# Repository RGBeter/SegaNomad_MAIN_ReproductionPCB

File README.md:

# Sega Nomad MAIN Reproduction PCB
Reproduction of the Sega Nomad's main board, created from scans provided by Villahed94, Sega's documentation, and community knowledge of the FC1004 style Genesis.
Additional features include TMSS bypass jumpers, SMS support and 32X support.

# Build Notes
These PCBs are tested to work with with a stock VENUS SUB pcb, building these requires skills in microsoldering, QFP soldering, hot air rework, and Mega Drive troubleshooting.
It is highly recomendded you start with a set of known working parts from a donor MegaDrive. VA1, VA1.8 and VA3 Model 2 Sega Genesis/MegaDrive can provide all of the necessary custom chips needed for this build.
Support is not officially provided by neither RGBeter nor Villahed94 with building or debugging these PCBs.

# Production Notes
While Sega utlized a 2 layer PCB for the Nomad, it is best to order these as a 4 layer PCB in order to improve noise across the board
If you wish NOT to include the SRES bypass, add the following bodge wires in order to connect the original 315-5684 based SRES circuit.

# BOM
Most of, if not all parts can be directly transplanted from a donor Nomad Main board, however, some alterations have been made, and they are as follows:

R5 + R6, FM DAC limiting resistors best changed to 0 ohms when modding audio

All large MLCC capacitors can have their value increased to 10uF to improve noise

|Component|Value|Note|
|:--------|:----|:---|
|IC1|PLCC 68000|CPU|
|IC2|68K RAM|WORK RAM|
|IC3|FC1004/FF1004|MAIN ASIC|
|IC4|VIDEO RAM|VRAM|
|IC5|QFP Z80|Z80 CPU|
|IC6|Z80 RAM|ZRAM|
|IC7|LM809|SRES BYPASS ONLY|
|C1|10uF|1206 X7R|
|C2|10uF|1206 X7R|
|C3|10uF|1206 X7R|
|C4|47pF|0603 C0G 315-5708 ONLY|
|C5|100pF|0603 C0G|
|C6|100pF|0603 C0G|
|C7|22pF|0603 C0G|
|C8|1000pF|0603 C0G|
|C9|N/A|DOES NOT EXIST|
|C10|100pF|0603 C0G|
|C11|100pF|0603 C0G|
|C12|33pF|0603 C0G|
|C13|N/A|DOES NOT EXIST|
|C14|10uF|1206 X7R|
|C15|10uF|1206 X7R|
|C16|10uF|1206 X7R|
|C17|10uF|1206 X7R|
|C18|20pF|0603 C0G|
|C19|47pF|0603 C0G|
|C20|10uF|1206 X7R|
|C21|33pF|0603 C0G DO NOT POPULATE|
|C22|100pF|0603 C0G|
|C23|33pF|0603 C0G|
|C24|100pF|0603 C0G|
|C25|0.1uF|0603 X7R|
|C26|0.1uF|0603 X7R|
|C27|0.1uF|0603 X7R|
|C28|N/A|DO NOT POPULATE|
|C29|100pF|0603 C0G|
|C30|0.1uF|0603 X7R|
|C31|0.047uF|0603 X7R|
|C32|N/A|DO NOT POPULATE|
|C33|N/A|DOES NOT EXIST|
|C30|1uF|0603 X7R SRES BYPASSS ONLY|
|CE1|47uF 6v|SMD ELEC, CAN REPLACE WITH TANTALUM|
|CE2|47uF 6v|SMD ELEC, CAN REPLACE WITH TANTALUM|
|CE3|100uF 6v|SMD ELEC, CAN REPLACE WITH TANTALUM|
|CE4|47uF 6v|SMD ELEC, CAN REPLACE WITH TANTALUM|
|D1|SOD-923 DIODE|SRES BYPASS ONLY|
|OSC1|MCLK OSCILATOR, SQUARE PACKAGE|CHECK REGION|
|R1|150R|0603|
|R2|220R|0603|
|R3|2.2K|0603|
|R4|220R|0603|
|R5|0R|0603 DAC LIMITING RESISTOR|
|R6|0R|0603 DAC LIMITING RESISTOR|
|R7|2.2K|0603|
|R8|4.7K|0603|
|R9|100R|0603|
|R10|100R|0603|
|R11|2.2K|0603|
|R12|2.2K|0603|
|R13|5.6K|0603|
|R14|5.6K|0603|
|R15|5.6K|0603|
|R16|4.7K|0603|
|R17|4.7K|0603|
|R18|4.7K|0603|
|R19|1.2K|0603|
|R20|1.2K|0603|
|R21|1.2K|0603|
|R22|4.7K|0603|
|R23|1.0K|0603|
|R24|330R|0603|
|R25|330R|0603|
|R26|2.2K|0603|
|R27|100K|0603|
|RA1|4.7K|5X1206 BANK|
|RB1|2.2K|4X0603 BANK|
|RB2|100R|4X0603 BANK|
|RB3|100R|4X0603 BANK|
|RB4|100R|4X0603 BANK|
|RB5|100R|4X0603 BANK|
|RB6|100R|4X0603 BANK|

# Special Thanks
Oleg Endo: Found missing C31 and documented its value, provided EMI filter part numbers

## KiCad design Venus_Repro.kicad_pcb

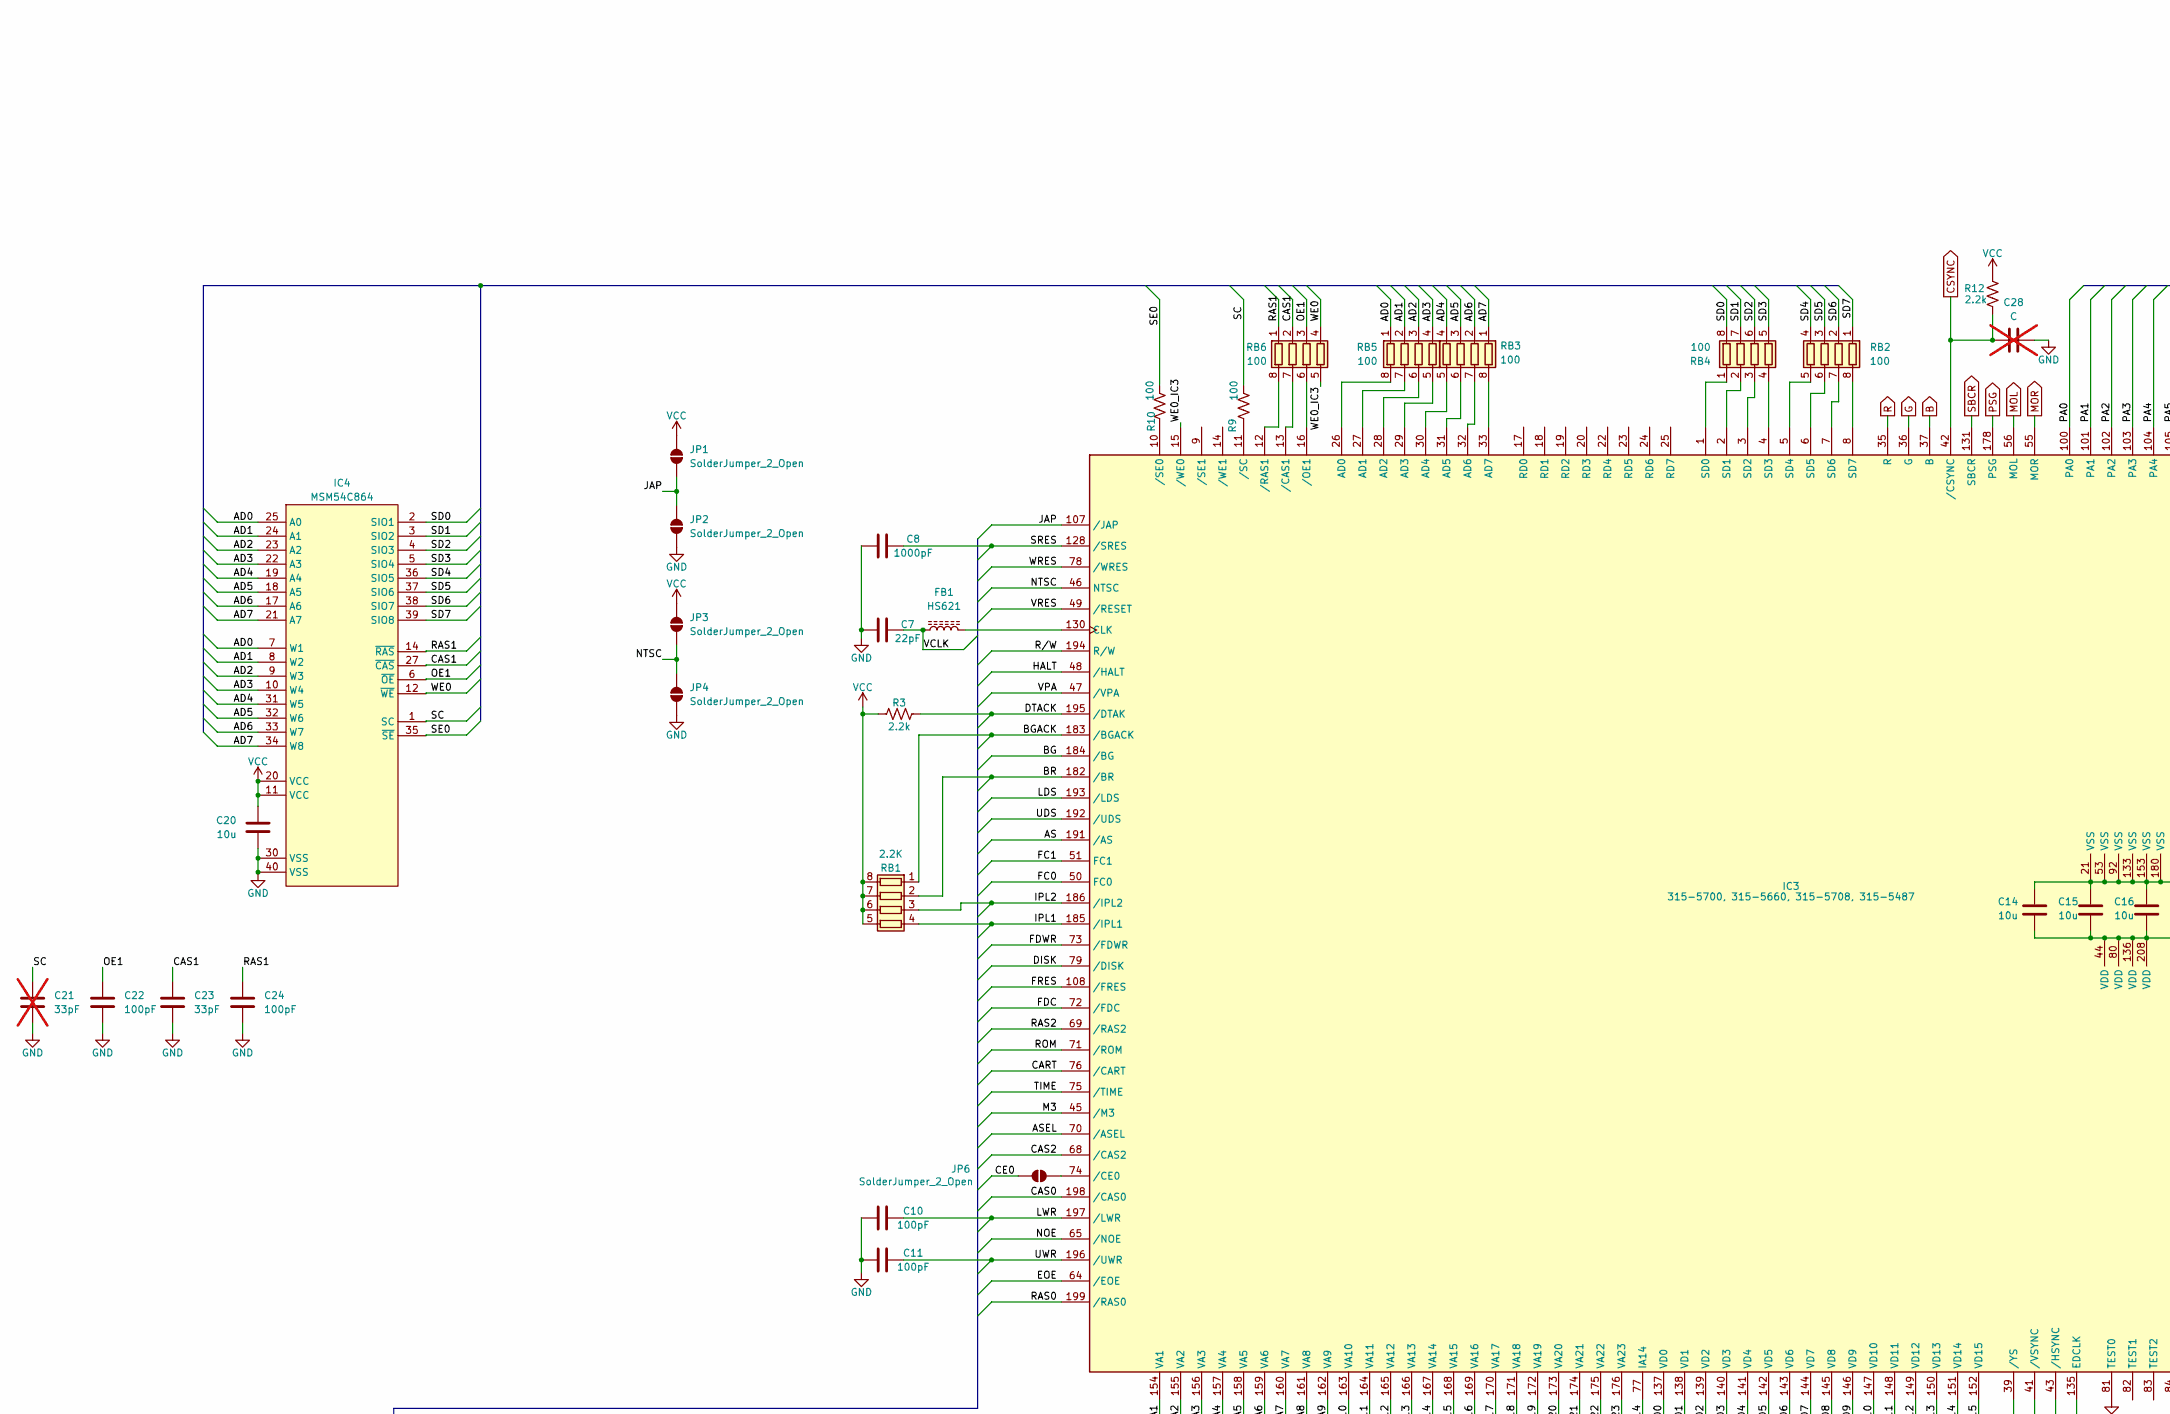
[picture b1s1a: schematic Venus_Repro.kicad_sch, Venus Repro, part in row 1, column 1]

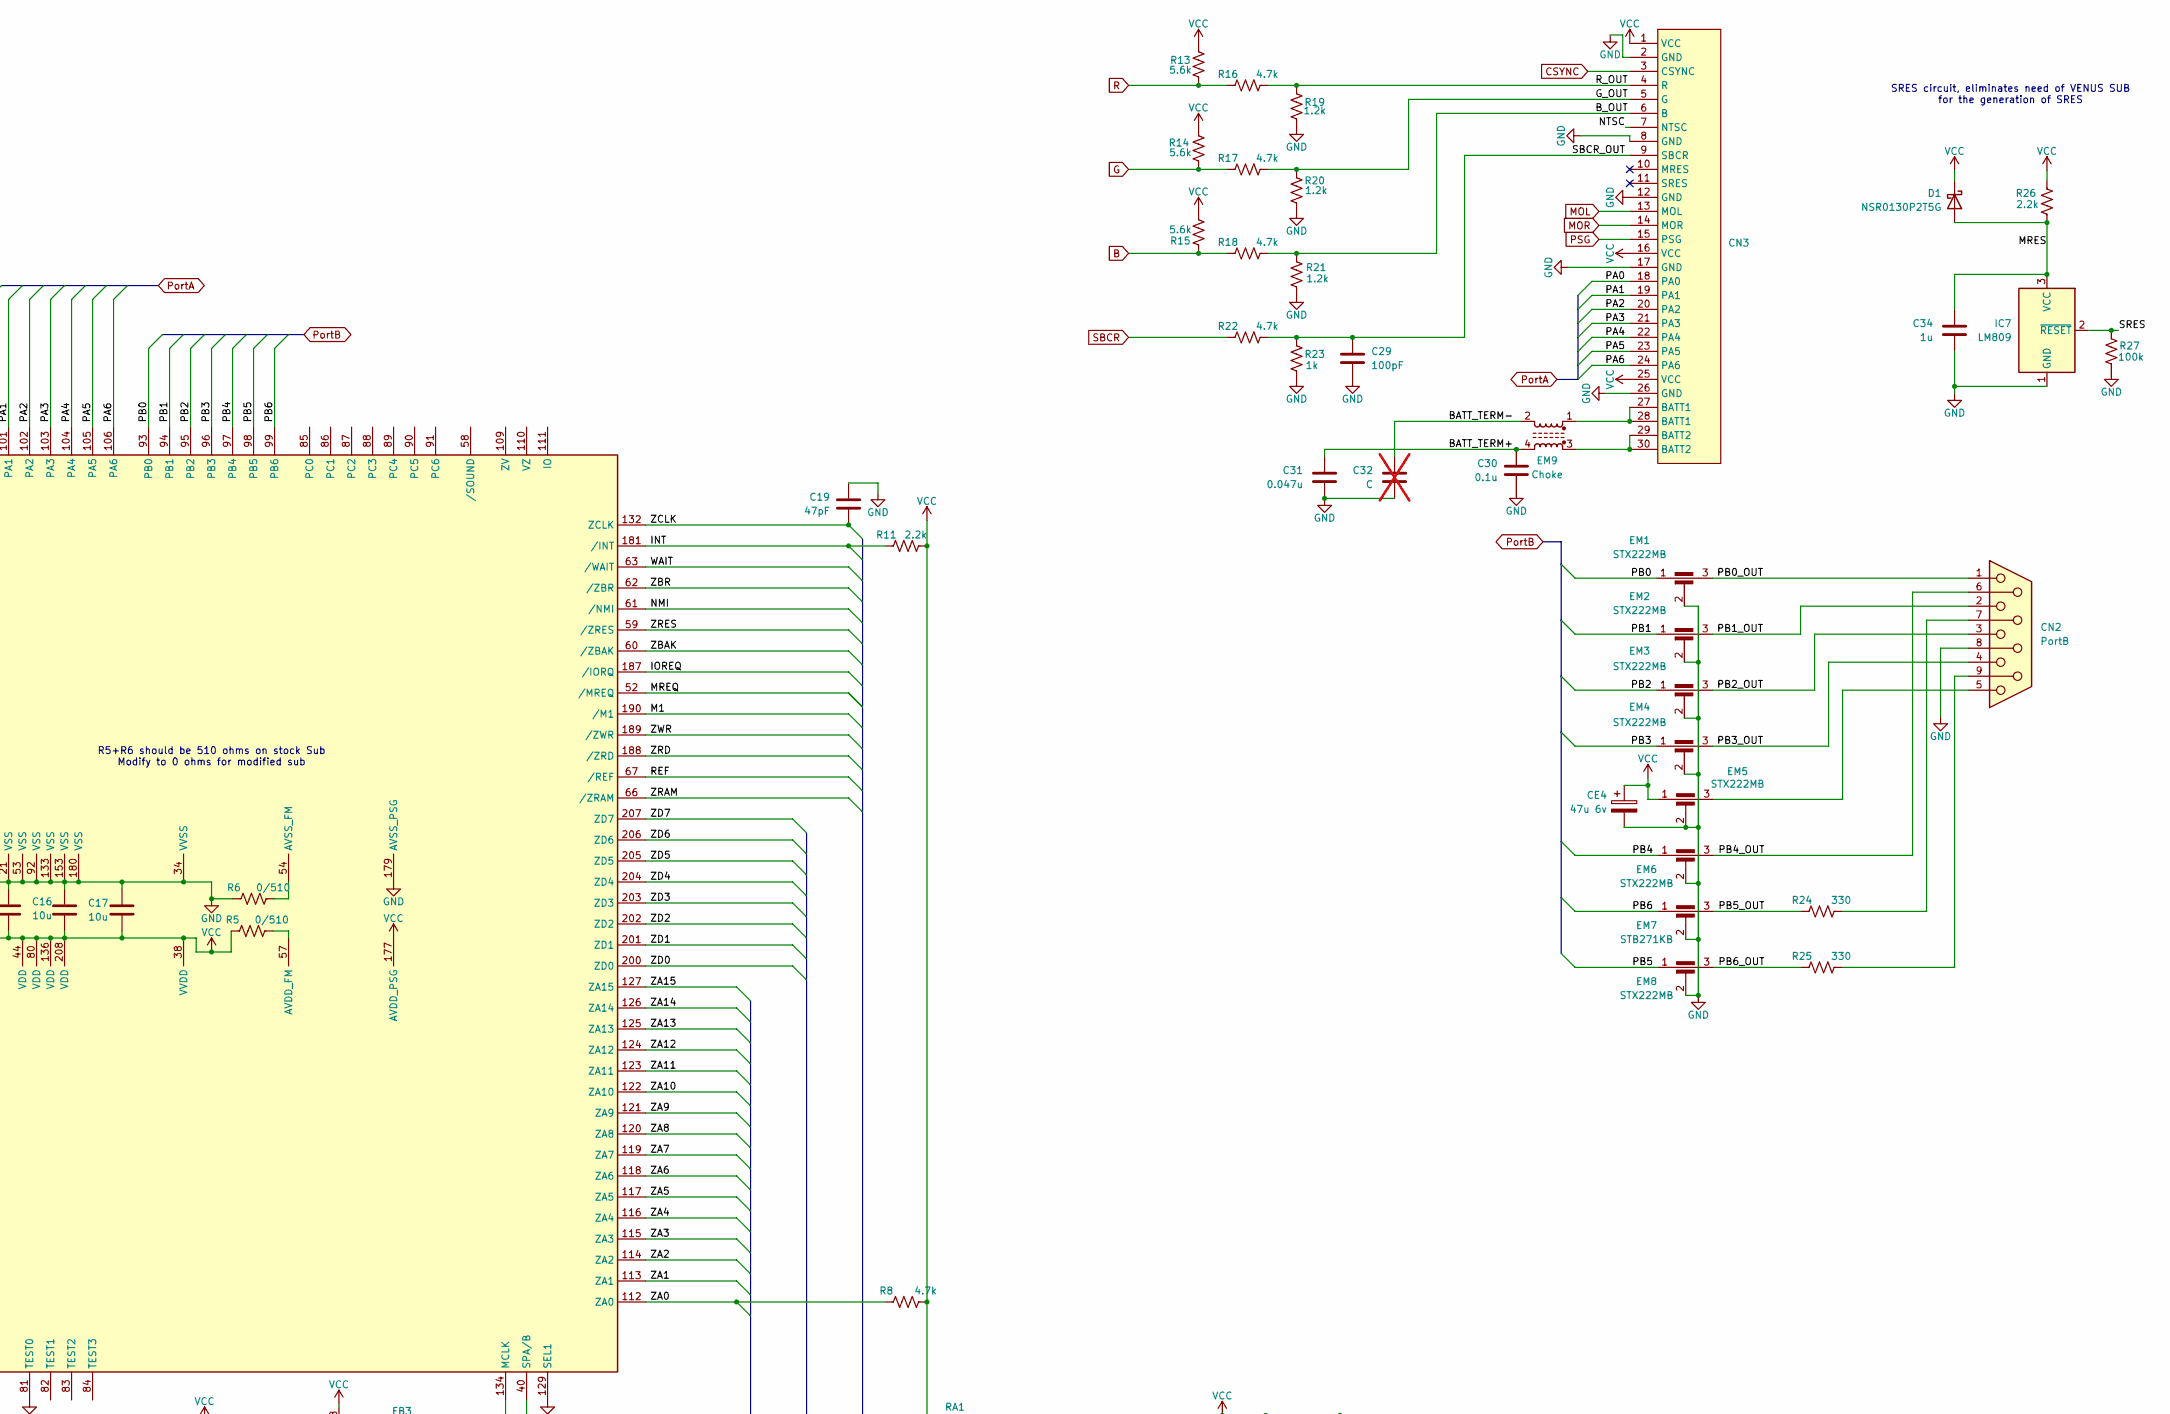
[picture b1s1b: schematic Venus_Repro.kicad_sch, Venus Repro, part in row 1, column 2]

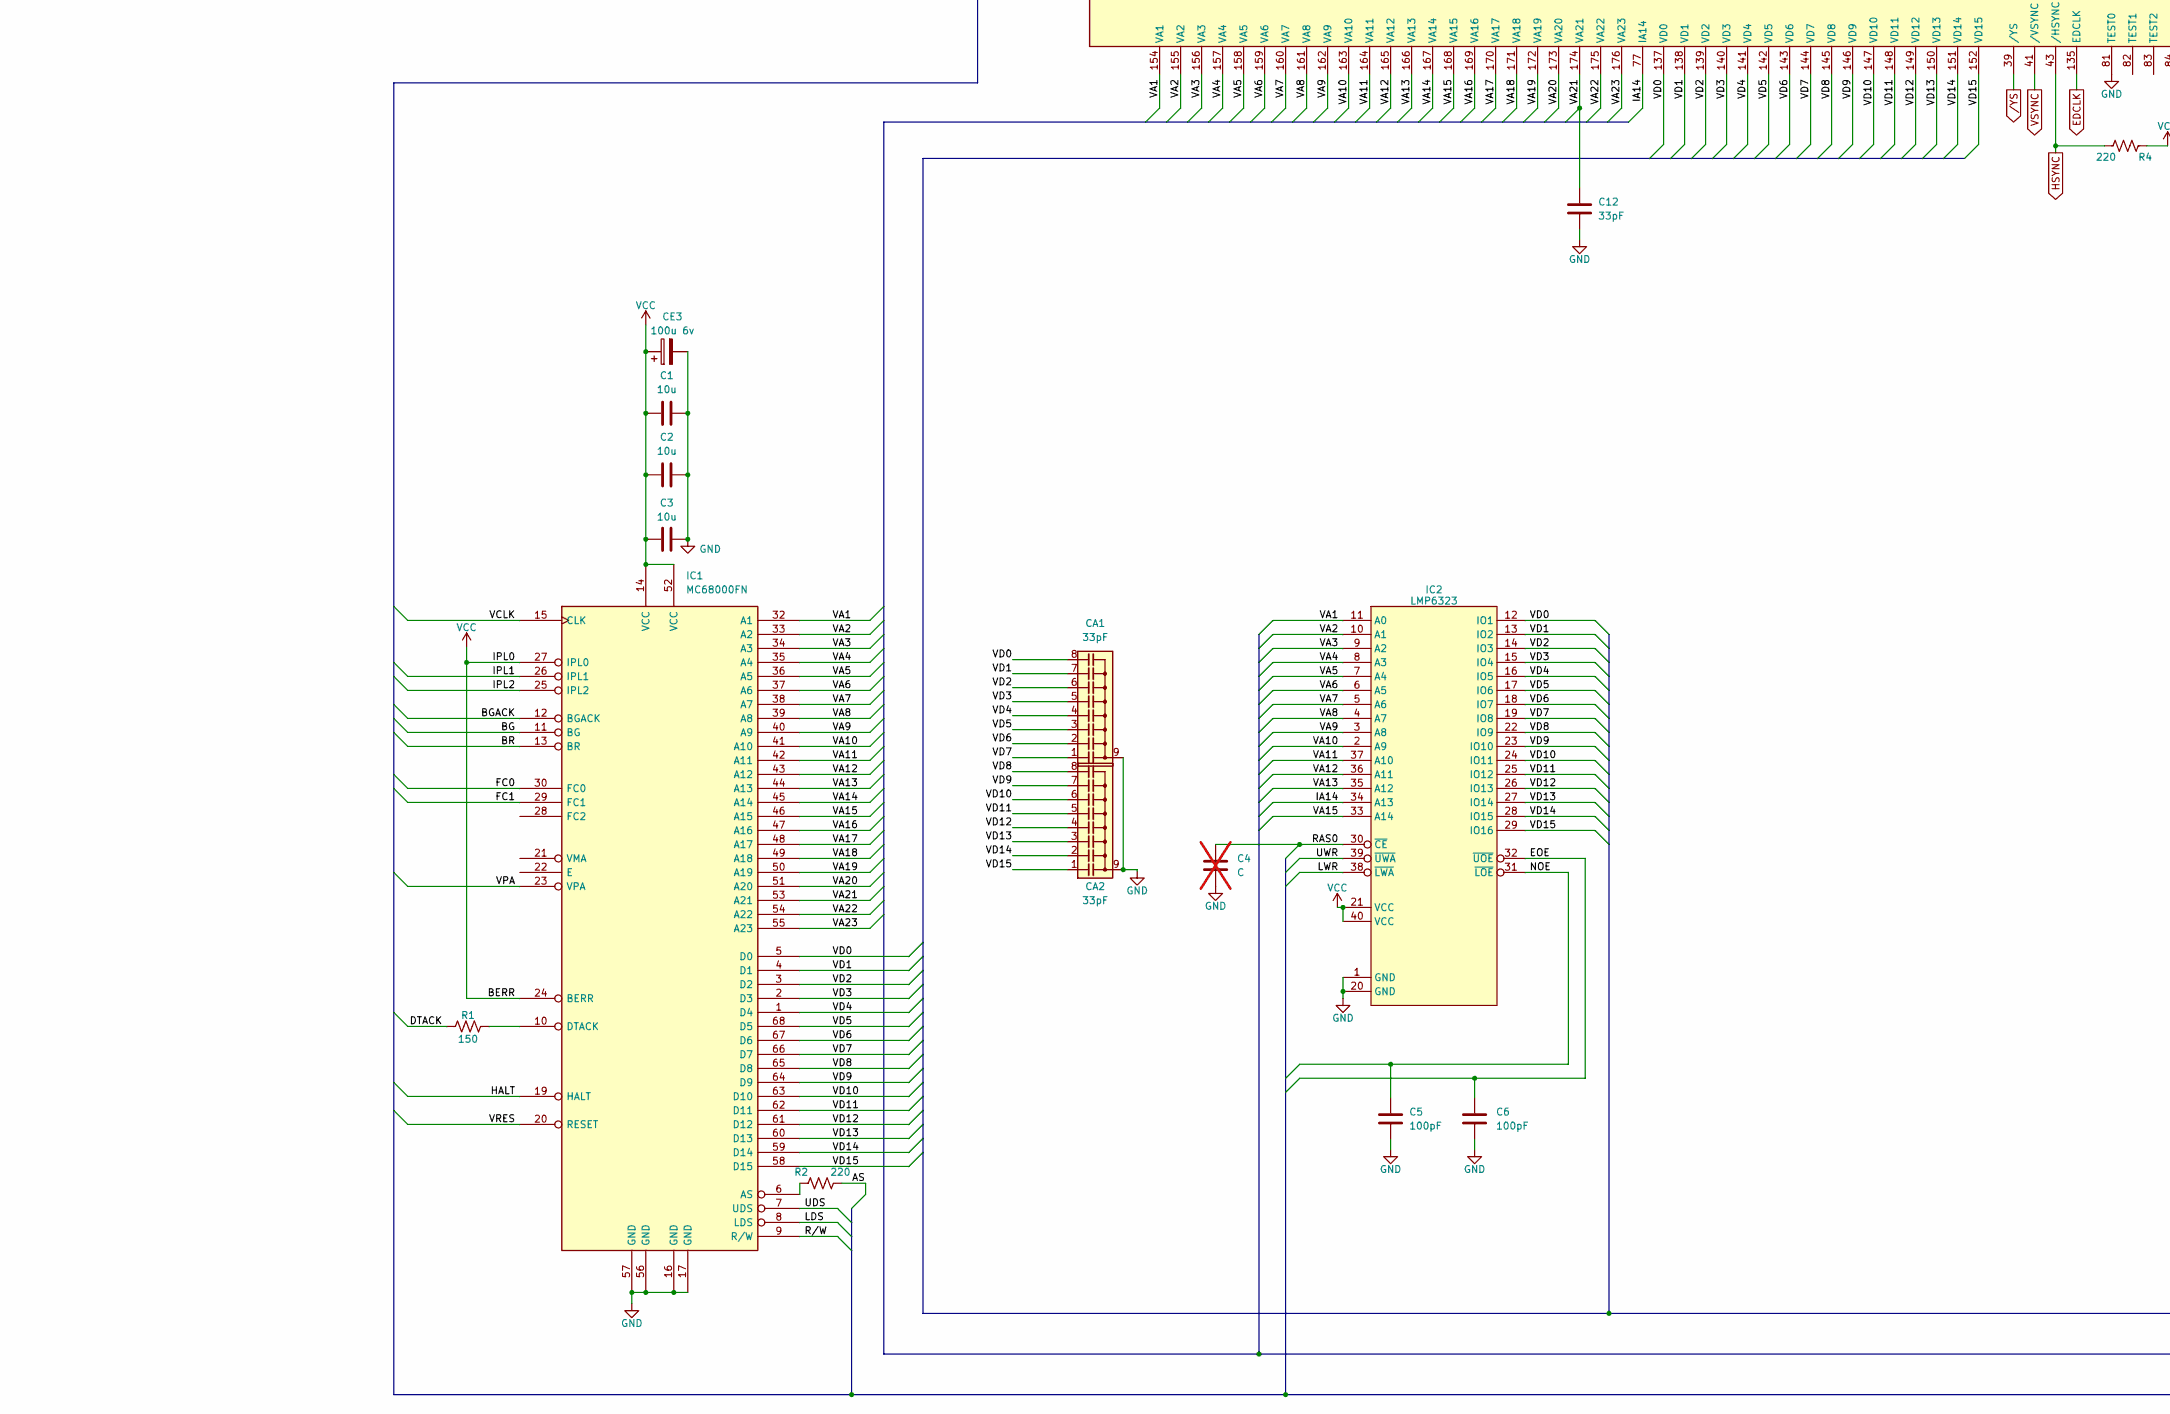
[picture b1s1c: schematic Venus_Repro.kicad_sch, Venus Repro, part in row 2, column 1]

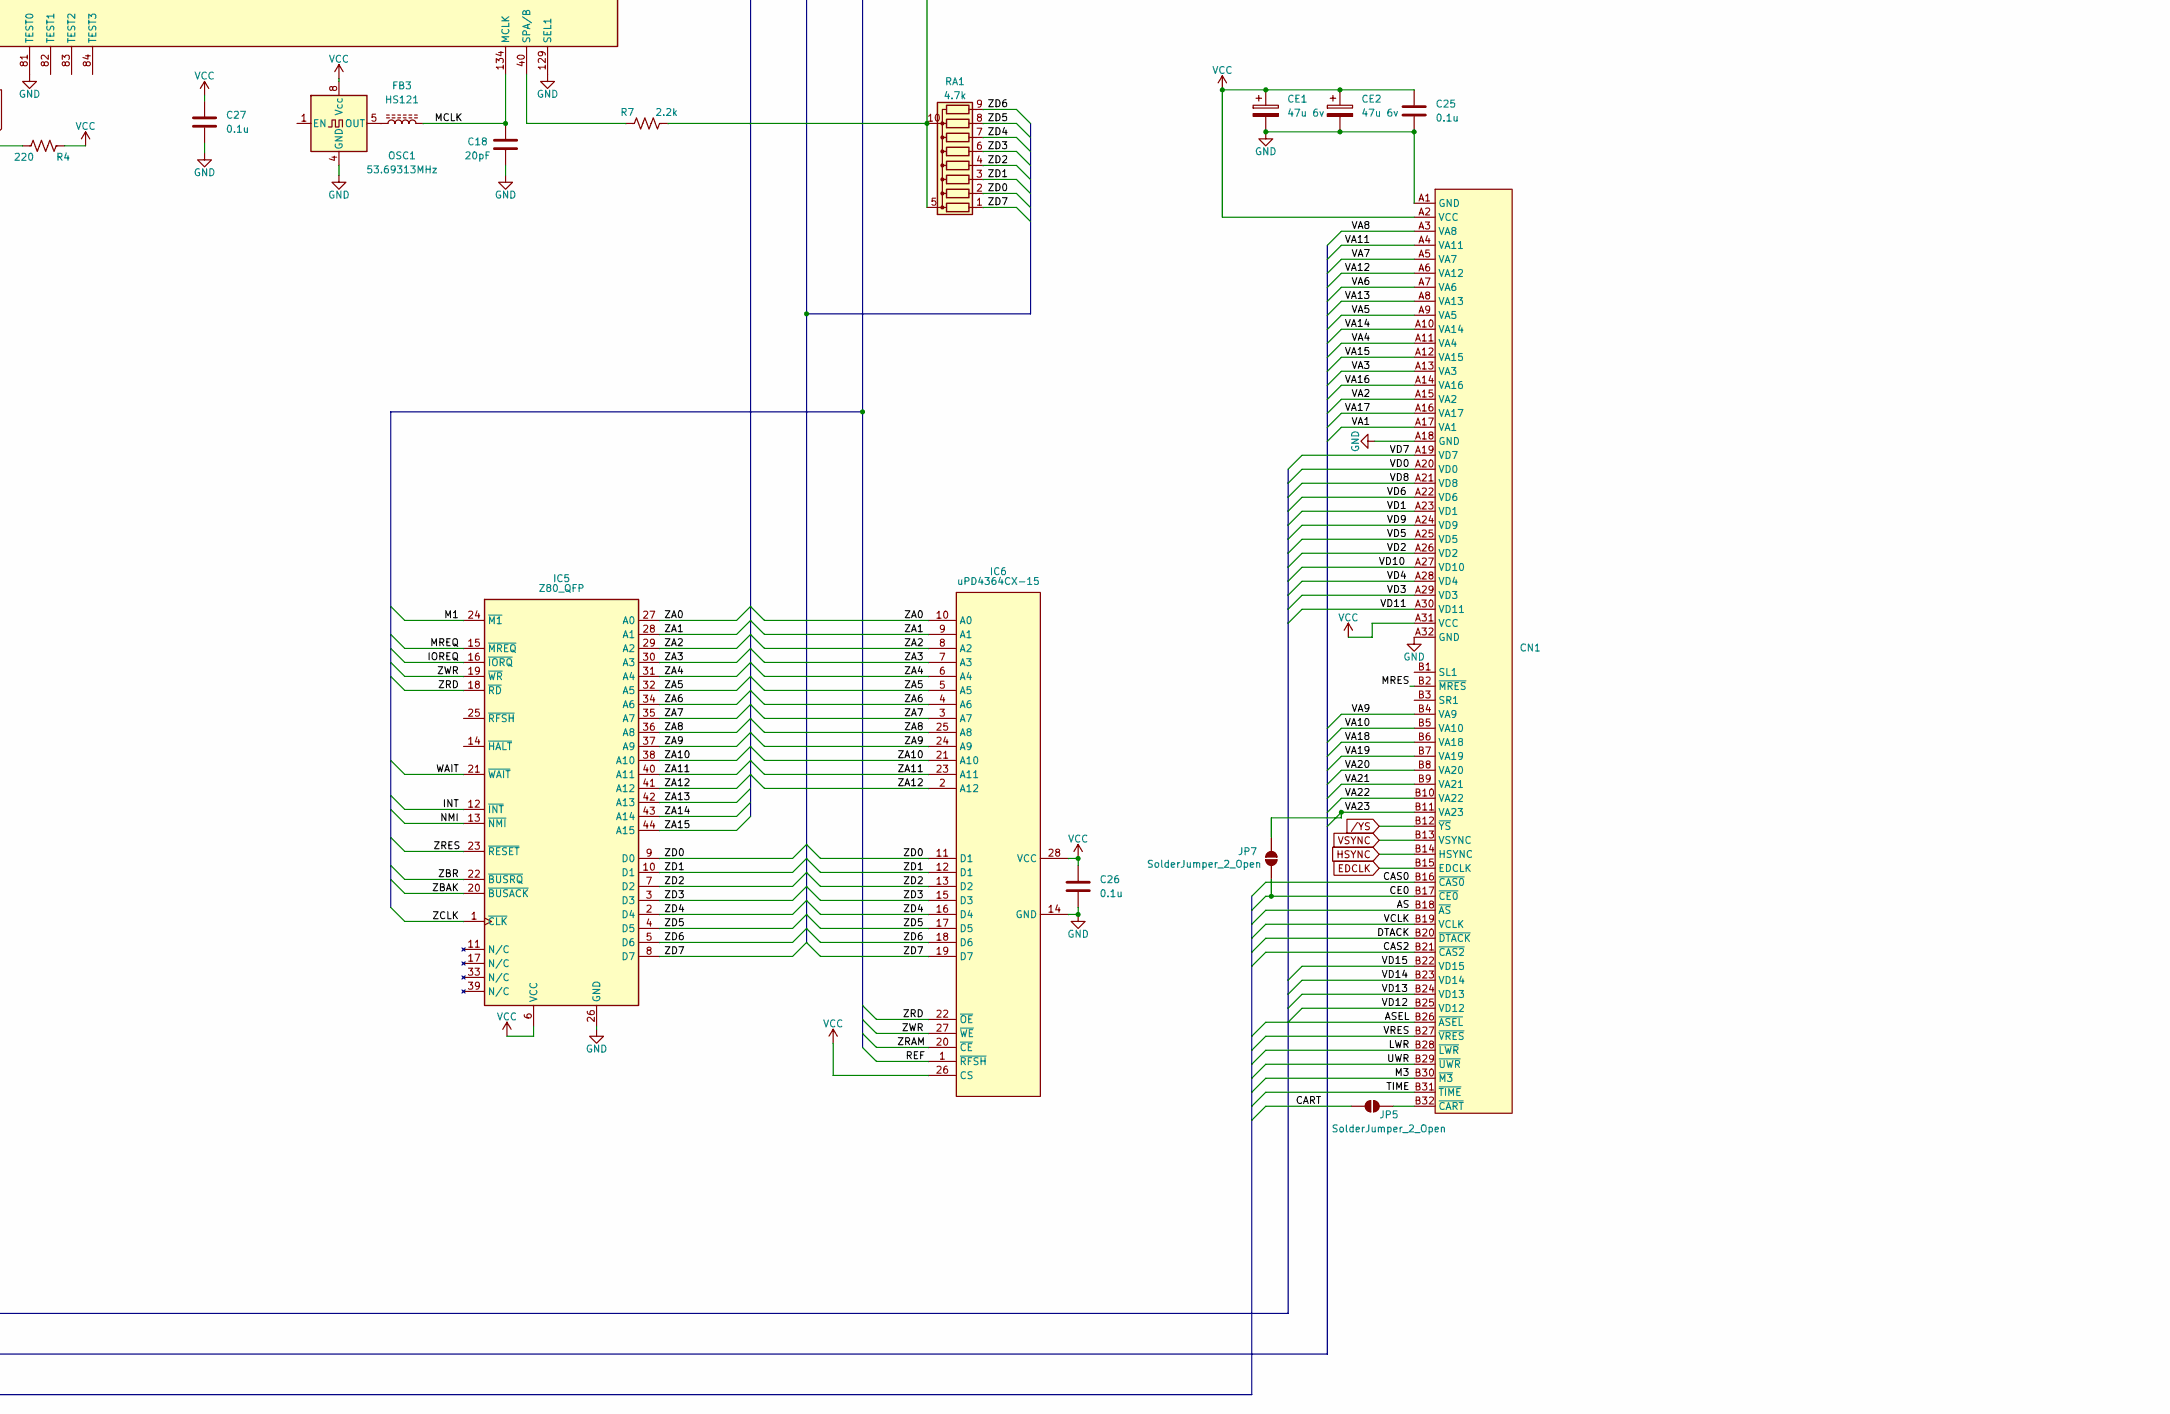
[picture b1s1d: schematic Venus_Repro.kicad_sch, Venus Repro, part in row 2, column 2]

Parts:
C1, C2, C3, C14, C15, C16, C17, C20: 10u; C_1206_3216Metric
C4, C28, C32: C; C_0603_1608Metric; not fitted
C5, C6, C10, C11, C22, C24, C29: 100pF; C_0603_1608Metric
C7: 22pF; C_0603_1608Metric
C8: 1000pF; C_0603_1608Metric
C12, C23: 33pF; C_0603_1608Metric
C18: 20pF; C_0603_1608Metric
C19: 47pF; C_0603_1608Metric
C21: 33pF; C_0603_1608Metric; not fitted
C25, C26, C27, C30: 0.1u; C_0603_1608Metric
C31: 0.047u; C_0603_1608Metric
C34: 1u; C_0603_1608Metric
CA1, CA2: 33pF; R_Array_Convex_4x1206
CE1, CE2, CE4: 47u 6v; CP_Elec_5x4.5
CE3: 100u 6v; CP_Elec_5x4.5
CN1: Venus_Cartidge_Slot
CN2: PortB; DSUB-9_Pins_Horizontal_P2.77x2.54mm_EdgePinOffset9.40mm
CN3: Venus_FFC
D1: NSR0130P2T5G; D_SOD-923
EM1, EM2, EM3, EM4, EM5, EM6, EM8: STX222MB; Venus_EMI
EM7: STB271KB; Venus_EMI
EM9: Choke; L_CommonModeChoke
FB1: HS621; L_0603_1608Metric
FB3: HS121; L_0603_1608Metric
IC1: MC68000FN; PLCC-68
IC2: LMP6323; Venus_WRAM
IC3: 315-5700, 315-5660, 315-5708, 315-5487; LQFP-208_28x28mm_P0.5mm
IC4: MSM54C864; SOJ-40
IC5: Z80_QFP; LQFP-44_Z80_10x10mm_P0.8mm
IC6: uPD4364CX-15; SOIC-28W_7.5x18.7mm_P1.27mm
IC7: LM809; SOT-23
JP1, JP2, JP3, JP4: SolderJumper_2_Open; SolderJumper-2_P1.3mm_Open_RoundedPad1.0x1.5mm
JP5, JP6, JP7: SolderJumper_2_Open; SolderJumper-2_P1.3mm_Open_Pad1.0x1.5mm
OSC1: 53.69313MHz; Oscillator_DIP-8
R1: 150; R_0603_1608Metric
R2, R4: 220; R_0603_1608Metric
R3, R7, R11, R12, R26: 2.2k; R_0603_1608Metric
R5, R6: 0/510; R_0603_1608Metric
R8, R16, R17, R18, R22: 4.7k; R_0603_1608Metric
R9, R10: 100; R_0603_1608Metric
R13, R14, R15: 5.6k; R_0603_1608Metric
R19, R20, R21: 1.2k; R_0603_1608Metric
R23: 1k; R_0603_1608Metric
R24, R25: 330; R_0603_1608Metric
R27: 100k; R_0603_1608Metric
RA1: 4.7k; R_Array_Convex_5x1206
RB1: 2.2K; R_Array_Convex_4x0603
RB2, RB3, RB4, RB5, RB6: 100; R_Array_Convex_4x0603

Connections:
/AD0: IC4.7 (W1), IC4.25 (A0), RB5.1 (R1.1)
/AD1: IC4.8 (W2), IC4.24 (A1), RB5.2 (R2.1)
/AD2: IC4.9 (W3), IC4.23 (A2), RB5.3 (R3.1)
/AD3: IC4.10 (W4), IC4.22 (A3), RB5.4 (R4.1)
/AD4: IC4.19 (A4), IC4.31 (W5), RB3.4 (R4.1)
/AD5: IC4.18 (A5), IC4.32 (W6), RB3.3 (R3.1)
/AD6: IC4.17 (A6), IC4.33 (W7), RB3.2 (R2.1)
/AD7: IC4.21 (A7), IC4.34 (W8), RB3.1 (R1.1)
/AS: CN1.B18 (~AS), IC3.191 (/AS), R2.2
/ASEL: CN1.B26 (~ASEL), IC3.70 (/ASEL)
/BATT_TERM+: C30.2, C31.1, EM9.4
/BATT_TERM-: C32.1, EM9.2
/BG: IC1.11 (BG), IC3.184 (/BG)
/BGACK: IC1.12 (BGACK), IC3.183 (/BGACK), RB1.1 (R1.1)
/BR: IC1.13 (BR), IC3.182 (/BR), RB1.2 (R2.1)
/B_OUT: CN3.6 (B), R18.2, R21.2
/CART: IC3.76 (/CART), JP5.2 (B)
/CAS0: CN1.B16 (~CAS0), IC3.198 (/CAS0)
/CAS1: C23.1, IC4.27 (~CAS), RB6.2 (R2.1)
/CAS2: CN1.B21 (~CAS2), IC3.68 (/CAS2)
/CE0: CN1.B17 (~CE0), JP6.1 (A), JP7.2 (B)
/DISK: IC3.79 (/DISK)
/DTACK: CN1.B20 (~DTACK), IC3.195 (/DTAK), R1.1, R3.2
/EOE: C6.1, IC2.32 (~UOE), IC3.64 (/EOE)
/FC0: IC1.30 (FC0), IC3.50 (FC0)
/FC1: IC1.29 (FC1), IC3.51 (FC1)
/FDC: IC3.72 (/FDC)
/FDWR: IC3.73 (/FDWR)
/FRES: IC3.108 (/FRES)
/G_OUT: CN3.5 (G), R17.2, R20.2
/HALT: IC1.19 (HALT), IC3.48 (/HALT)
/IA14: IC2.34 (A13), IC3.77 (IA14)
/INT: IC3.181 (/INT), IC5.12 (~INT), R11.1
/IOREQ: IC3.187 (/IORQ), IC5.16 (~IORQ)
/IPL1: IC1.26 (IPL1), IC3.185 (/IPL1), RB1.4 (R4.1)
/IPL2: IC1.25 (IPL2), IC3.186 (/IPL2), RB1.3 (R3.1)
/JAP: IC3.107 (/JAP), JP1.1 (A), JP2.2 (B)
/LDS: IC1.8 (LDS), IC3.193 (/LDS)
/LWR: C10.2, CN1.B28 (~LWR), IC2.38 (~LWA), IC3.197 (/LWR)
/M1: IC3.190 (/M1), IC5.24 (~M1)
/M3: CN1.B30 (~M3), IC3.45 (/M3)
/MCLK: C18.1, FB3.2, IC3.134 (MCLK)
/MREQ: IC3.52 (/MREQ), IC5.15 (~MREQ)
/MRES: C34.1, CN1.B2 (~MRES), D1.2 (A), IC7.3 (VCC), R26.1
/NMI: IC3.61 (/NMI), IC5.13 (~NMI)
/NOE: C5.2, IC2.31 (~LOE), IC3.65 (/NOE)
/NTSC: CN3.7 (NTSC), IC3.46 (NTSC), JP3.1 (A), JP4.2 (B)
/OE1: C22.1, IC4.6 (~OE), RB6.3 (R3.1)
/PA0: CN3.18 (PA0), IC3.100 (PA0)
/PA1: CN3.19 (PA1), IC3.101 (PA1)
/PA2: CN3.20 (PA2), IC3.102 (PA2)
/PA3: CN3.21 (PA3), IC3.103 (PA3)
/PA4: CN3.22 (PA4), IC3.104 (PA4)
/PA5: CN3.23 (PA5), IC3.105 (PA5)
/PA6: CN3.24 (PA6), IC3.106 (PA6)
/PB0: EM1.1, IC3.93 (PB0)
/PB0_OUT: CN2.1, EM1.3
/PB1: EM2.1, IC3.94 (PB1)
/PB1_OUT: CN2.2, EM2.3
/PB2: EM3.1, IC3.95 (PB2)
/PB2_OUT: CN2.3, EM3.3
/PB3: EM4.1, IC3.96 (PB3)
/PB3_OUT: CN2.4, EM4.3
/PB4: EM6.1, IC3.97 (PB4)
/PB4_OUT: CN2.6, EM6.3
/PB5: EM8.1, IC3.98 (PB5)
/PB5_OUT: EM7.3, R24.1
/PB6: EM7.1, IC3.99 (PB6)
/PB6_OUT: EM8.3, R25.1
/RAS0: C4.1, IC2.30 (~CE), IC3.199 (/RAS0)
/RAS1: C24.1, IC4.14 (~RAS), RB6.1 (R1.1)
/RAS2: IC3.69 (/RAS2)
/REF: IC3.67 (/REF), IC6.1 (~RFSH)
/ROM: IC3.71 (/ROM)
/R_OUT: CN3.4 (R), R16.2, R19.1
/R/W: IC1.9 (R/W), IC3.194 (R/W)
/SBCR_OUT: C29.2, CN3.9 (SBCR), R22.2, R23.2
/SC: C21.1, IC4.1 (SC), R9.2
/SD0: IC4.2 (SIO1), RB4.8 (R1.2)
/SD1: IC4.3 (SIO2), RB4.7 (R2.2)
/SD2: IC4.4 (SIO3), RB4.6 (R3.2)
/SD3: IC4.5 (SIO4), RB4.5 (R4.2)
/SD4: IC4.36 (SIO5), RB2.4 (R4.1)
/SD5: IC4.37 (SIO6), RB2.3 (R3.1)
/SD6: IC4.38 (SIO7), RB2.2 (R2.1)
/SD7: IC4.39 (SIO8), RB2.1 (R1.1)
/SE0: IC4.35 (~SE), R10.2
/SRES: C8.2, IC3.128 (/SRES), IC7.2 (~RESET), R27.2
/TIME: CN1.B31 (~TIME), IC3.75 (/TIME)
/UDS: IC1.7 (UDS), IC3.192 (/UDS)
/UWR: C11.2, CN1.B29 (~UWR), IC2.39 (~UWA), IC3.196 (/UWR)
/VA1: CN1.A17 (VA1), IC1.32 (A1), IC2.11 (A0), IC3.154 (VA1)
/VA2: CN1.A15 (VA2), IC1.33 (A2), IC2.10 (A1), IC3.155 (VA2)
/VA3: CN1.A13 (VA3), IC1.34 (A3), IC2.9 (A2), IC3.156 (VA3)
/VA4: CN1.A11 (VA4), IC1.35 (A4), IC2.8 (A3), IC3.157 (VA4)
/VA5: CN1.A9 (VA5), IC1.36 (A5), IC2.7 (A4), IC3.158 (VA5)
/VA6: CN1.A7 (VA6), IC1.37 (A6), IC2.6 (A5), IC3.159 (VA6)
/VA7: CN1.A5 (VA7), IC1.38 (A7), IC2.5 (A6), IC3.160 (VA7)
/VA8: CN1.A3 (VA8), IC1.39 (A8), IC2.4 (A7), IC3.161 (VA8)
/VA9: CN1.B4 (VA9), IC1.40 (A9), IC2.3 (A8), IC3.162 (VA9)
/VA10: CN1.B5 (VA10), IC1.41 (A10), IC2.2 (A9), IC3.163 (VA10)
/VA11: CN1.A4 (VA11), IC1.42 (A11), IC2.37 (A10), IC3.164 (VA11)
/VA12: CN1.A6 (VA12), IC1.43 (A12), IC2.36 (A11), IC3.165 (VA12)
/VA13: CN1.A8 (VA13), IC1.44 (A13), IC2.35 (A12), IC3.166 (VA13)
/VA14: CN1.A10 (VA14), IC1.45 (A14), IC3.167 (VA14)
/VA15: CN1.A12 (VA15), IC1.46 (A15), IC2.33 (A14), IC3.168 (VA15)
/VA16: CN1.A14 (VA16), IC1.47 (A16), IC3.169 (VA16)
/VA17: CN1.A16 (VA17), IC1.48 (A17), IC3.170 (VA17)
/VA18: CN1.B6 (VA18), IC1.49 (A18), IC3.171 (VA18)
/VA19: CN1.B7 (VA19), IC1.50 (A19), IC3.172 (VA19)
/VA20: CN1.B8 (VA20), IC1.51 (A20), IC3.173 (VA20)
/VA21: C12.2, CN1.B9 (VA21), IC1.53 (A21), IC3.174 (VA21)
/VA22: CN1.B10 (VA22), IC1.54 (A22), IC3.175 (VA22)
/VA23: CN1.B11 (VA23), IC1.55 (A23), IC3.176 (VA23), JP7.1 (A)
/VCLK: C7.2, CN1.B19 (VCLK), FB1.1, IC1.15 (CLK)
/VD0: CA1.8 (C7), CN1.A20 (VD0), IC1.5 (D0), IC2.12 (IO1), IC3.137 (VD0)
/VD1: CA1.7 (C6), CN1.A23 (VD1), IC1.4 (D1), IC2.13 (IO2), IC3.138 (VD1)
/VD2: CA1.6 (C5), CN1.A26 (VD2), IC1.3 (D2), IC2.14 (IO3), IC3.139 (VD2)
/VD3: CA1.5 (C4), CN1.A29 (VD3), IC1.2 (D3), IC2.15 (IO4), IC3.140 (VD3)
/VD4: CA1.4 (C3), CN1.A28 (VD4), IC1.1 (D4), IC2.16 (IO5), IC3.141 (VD4)
/VD5: CA1.3 (C2), CN1.A25 (VD5), IC1.68 (D5), IC2.17 (IO6), IC3.142 (VD5)
/VD6: CA1.2 (C1), CN1.A22 (VD6), IC1.67 (D6), IC2.18 (IO7), IC3.143 (VD6)
/VD7: CA1.1 (C8), CN1.A19 (VD7), IC1.66 (D7), IC2.19 (IO8), IC3.144 (VD7)
/VD8: CA2.8 (C7), CN1.A21 (VD8), IC1.65 (D8), IC2.22 (IO9), IC3.145 (VD8)
/VD9: CA2.7 (C6), CN1.A24 (VD9), IC1.64 (D9), IC2.23 (IO10), IC3.146 (VD9)
/VD10: CA2.6 (C5), CN1.A27 (VD10), IC1.63 (D10), IC2.24 (IO11), IC3.147 (VD10)
/VD11: CA2.5 (C4), CN1.A30 (VD11), IC1.62 (D11), IC2.25 (IO12), IC3.148 (VD11)
/VD12: CA2.4 (C3), CN1.B25 (VD12), IC1.61 (D12), IC2.26 (IO13), IC3.149 (VD12)
/VD13: CA2.3 (C2), CN1.B24 (VD13), IC1.60 (D13), IC2.27 (IO14), IC3.150 (VD13)
/VD14: CA2.2 (C1), CN1.B23 (VD14), IC1.59 (D14), IC2.28 (IO15), IC3.151 (VD14)
/VD15: CA2.1 (C8), CN1.B22 (VD15), IC1.58 (D15), IC2.29 (IO16), IC3.152 (VD15)
/VPA: IC1.23 (VPA), IC3.47 (/VPA)
/VRES: CN1.B27 (~VRES), IC1.20 (RESET), IC3.49 (/RESET)
/WAIT: IC3.63 (/WAIT), IC5.21 (~WAIT)
/WE0: IC4.12 (~WE), RB6.4 (R4.1)
/WE0_IC3: IC3.15 (/WE0), RB6.5 (R4.2)
/WRES: IC3.78 (/WRES)
/ZA0: IC3.112 (ZA0), IC5.27 (A0), IC6.10 (A0), R8.1
/ZA1: IC3.113 (ZA1), IC5.28 (A1), IC6.9 (A1)
/ZA2: IC3.114 (ZA2), IC5.29 (A2), IC6.8 (A2)
/ZA3: IC3.115 (ZA3), IC5.30 (A3), IC6.7 (A3)
/ZA4: IC3.116 (ZA4), IC5.31 (A4), IC6.6 (A4)
/ZA5: IC3.117 (ZA5), IC5.32 (A5), IC6.5 (A5)
/ZA6: IC3.118 (ZA6), IC5.34 (A6), IC6.4 (A6)
/ZA7: IC3.119 (ZA7), IC5.35 (A7), IC6.3 (A7)
/ZA8: IC3.120 (ZA8), IC5.36 (A8), IC6.25 (A8)
/ZA9: IC3.121 (ZA9), IC5.37 (A9), IC6.24 (A9)
/ZA10: IC3.122 (ZA10), IC5.38 (A10), IC6.21 (A10)
/ZA11: IC3.123 (ZA11), IC5.40 (A11), IC6.23 (A11)
/ZA12: IC3.124 (ZA12), IC5.41 (A12), IC6.2 (A12)
/ZA13: IC3.125 (ZA13), IC5.42 (A13)
/ZA14: IC3.126 (ZA14), IC5.43 (A14)
/ZA15: IC3.127 (ZA15), IC5.44 (A15)
/ZBAK: IC3.60 (/ZBAK), IC5.20 (~BUSACK)
/ZBR: IC3.62 (/ZBR), IC5.22 (~BUSRQ)
/ZCLK: C19.1, IC3.132 (ZCLK), IC5.1 (~CLK)
/ZD0: IC3.200 (ZD0), IC5.9 (D0), IC6.11 (D1), RA1.2 (R2)
/ZD1: IC3.201 (ZD1), IC5.10 (D1), IC6.12 (D1), RA1.3 (R3)
/ZD2: IC3.202 (ZD2), IC5.7 (D2), IC6.13 (D2), RA1.4 (R4)
/ZD3: IC3.203 (ZD3), IC5.3 (D3), IC6.15 (D3), RA1.6 (R5)
/ZD4: IC3.204 (ZD4), IC5.2 (D4), IC6.16 (D4), RA1.7 (R6)
/ZD5: IC3.205 (ZD5), IC5.4 (D5), IC6.17 (D5), RA1.8 (R7)
/ZD6: IC3.206 (ZD6), IC5.5 (D6), IC6.18 (D6), RA1.9 (R8)
/ZD7: IC3.207 (ZD7), IC5.8 (D7), IC6.19 (D7), RA1.1 (R1)
/ZRAM: IC3.66 (/ZRAM), IC6.20 (~CE)
/ZRD: IC3.188 (/ZRD), IC5.18 (~RD), IC6.22 (~OE)
/ZRES: IC3.59 (/ZRES), IC5.23 (~RESET)
/ZWR: IC3.189 (/ZWR), IC5.19 (~WR), IC6.27 (~WE)
B: IC3.37 (B), R15.1, R18.1
CSYNC: C28.1, CN3.3 (CSYNC), IC3.42 (/CSYNC), R12.1
EDCLK: CN1.B15 (EDCLK), IC3.135 (EDCLK)
G: IC3.36 (G), R14.1, R17.1
GND: C1.2, C2.2, C3.2, C4.2, C5.1, C6.2, C7.1, C8.1, C10.1, C11.1, C12.1, C14.2, C15.2, C16.2, C17.2, C18.2, C19.2, C20.2, C21.2, C22.2, C23.2, C24.2, C25.2, C26.2, C27.2, C28.2, C29.1, C30.1, C31.2, C32.2, C34.2, CA1.9 (common), CA2.9 (common), CE1.2, CE2.2, CE3.2, CE4.2, CN1.A1 (GND), CN1.A18 (GND), CN1.A32 (GND), CN2.8, CN3.2 (GND), CN3.8 (GND), CN3.12 (GND), CN3.17 (GND), CN3.26 (GND), EM1.2, EM2.2, EM3.2, EM4.2, EM5.2, EM6.2, EM7.2, EM8.2, IC1.16 (GND), IC1.17 (GND), IC1.56 (GND), IC1.57 (GND), IC2.1 (GND), IC2.20 (GND), IC3.21 (VSS), IC3.34 (VVSS), IC3.53 (VSS), IC3.81 (TEST0), IC3.92 (VSS), IC3.129 (SEL1), IC3.133 (VSS), IC3.153 (VSS), IC3.179 (AVSS_PSG), IC3.180 (VSS), IC4.30 (VSS), IC4.40 (VSS), IC5.26 (GND), IC6.14 (GND), IC7.1 (GND), JP2.1 (A), JP4.1 (A), OSC1.4 (GND), R6.1, R19.2, R20.1, R21.1, R23.1, R27.1
HSYNC: CN1.B14 (HSYNC), IC3.43 (/HSYNC), R4.2
MOL: CN3.13 (MOL), IC3.56 (MOL)
MOR: CN3.14 (MOR), IC3.55 (MOR)
unnamed: CN1.B32 (~CART), JP5.1 (A)
unnamed: CN2.5, EM5.3
unnamed: CN2.7, R24.2
unnamed: CN2.9, R25.2
unnamed: CN3.27 (BATT1), CN3.28 (BATT1), EM9.1
unnamed: CN3.29 (BATT2), CN3.30 (BATT2), EM9.3
unnamed: IC1.6 (AS), R2.1
unnamed: IC1.10 (DTACK), R1.2
unnamed: IC3.26 (AD0), RB5.8 (R1.2)
unnamed: IC3.27 (AD1), RB5.7 (R2.2)
unnamed: IC3.28 (AD2), RB5.6 (R3.2)
unnamed: IC3.29 (AD3), RB5.5 (R4.2)
unnamed: IC3.30 (AD4), RB3.5 (R4.2)
unnamed: IC3.31 (AD5), RB3.6 (R3.2)
unnamed: IC3.32 (AD6), RB3.7 (R2.2)
unnamed: IC3.33 (AD7), RB3.8 (R1.2)
unnamed: IC3.57 (AVDD_FM), R5.2
unnamed: IC3.54 (AVSS_FM), R6.2
unnamed: FB1.2, IC3.130 (CLK)
unnamed: IC3.1 (SD0), RB4.1 (R1.1)
unnamed: IC3.2 (SD1), RB4.2 (R2.1)
unnamed: IC3.3 (SD2), RB4.3 (R3.1)
unnamed: IC3.4 (SD3), RB4.4 (R4.1)
unnamed: IC3.5 (SD4), RB2.5 (R4.2)
unnamed: IC3.6 (SD5), RB2.6 (R3.2)
unnamed: IC3.7 (SD6), RB2.7 (R2.2)
unnamed: IC3.8 (SD7), RB2.8 (R1.2)
unnamed: IC3.40 (SPA/B), R7.1
unnamed: IC3.13 (/CAS1), RB6.7 (R2.2)
unnamed: IC3.74 (/CE0), JP6.2 (B)
unnamed: IC3.16 (/OE1), RB6.6 (R3.2)
unnamed: IC3.12 (/RAS1), RB6.8 (R1.2)
unnamed: IC3.11 (/SC), R9.1
unnamed: IC3.10 (/SE0), R10.1
unnamed: FB3.1, OSC1.5 (OUT)
PSG: CN3.15 (PSG), IC3.178 (PSG)
R: IC3.35 (R), R13.1, R16.1
SBCR: IC3.131 (SBCR), R22.1
VCC: C1.1, C2.1, C3.1, C14.1, C15.1, C16.1, C17.1, C20.1, C25.1, C26.1, C27.1, CE1.1, CE2.1, CE3.1, CE4.1, CN1.A2 (VCC), CN1.A31 (VCC), CN3.1 (VCC), CN3.16 (VCC), CN3.25 (VCC), D1.1 (K), EM5.1, IC1.14 (VCC), IC1.24 (BERR), IC1.27 (IPL0), IC1.52 (VCC), IC2.21 (VCC), IC2.40 (VCC), IC3.38 (VVDD), IC3.44 (VDD), IC3.80 (VDD), IC3.136 (VDD), IC3.177 (AVDD_PSG), IC3.208 (VDD), IC4.11 (VCC), IC4.20 (VCC), IC5.6 (VCC), IC6.26 (CS), IC6.28 (VCC), JP1.2 (B), JP3.2 (B), OSC1.8 (Vcc), R3.1, R4.1, R5.1, R7.2, R8.2, R11.2, R12.2, R13.2, R14.2, R15.2, R26.2, RA1.5 (common), RA1.10 (common), RB1.5 (R4.2), RB1.6 (R3.2), RB1.7 (R2.2), RB1.8 (R1.2)
VSYNC: CN1.B13 (VSYNC), IC3.41 (/VSYNC)
/YS: CN1.B12 (~YS), IC3.39 (/YS)

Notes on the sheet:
SRES circuit, eliminates need of VENUS SUB for the generation of SRES
R5+R6 should be 510 ohms on stock Sub Modify to 0 ohms for modified sub

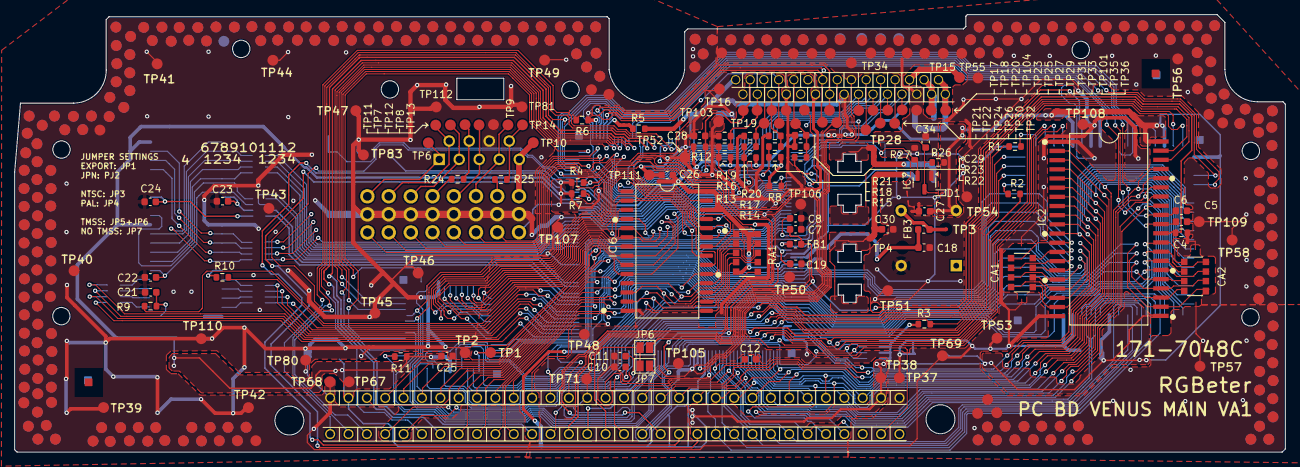
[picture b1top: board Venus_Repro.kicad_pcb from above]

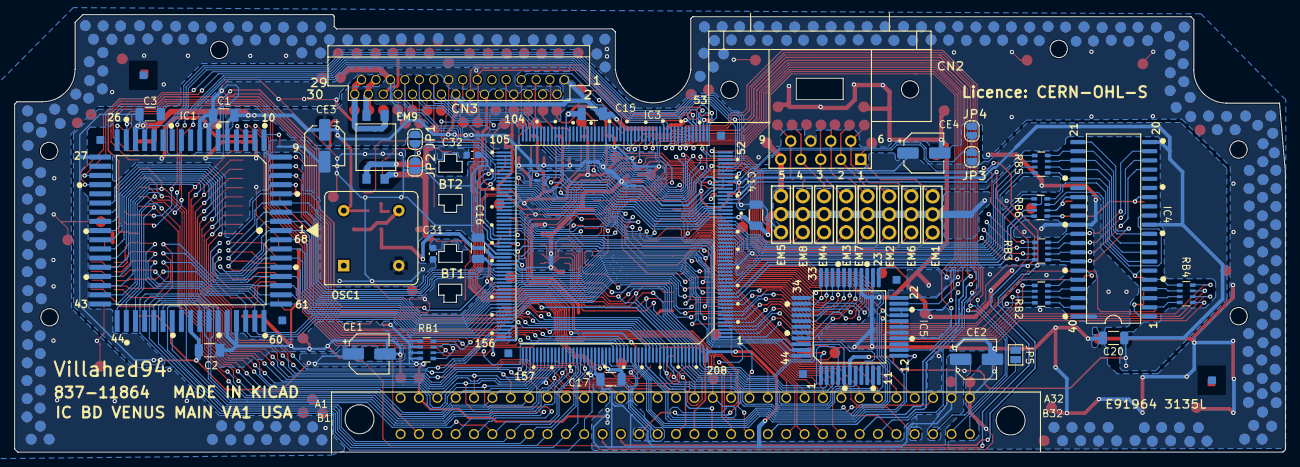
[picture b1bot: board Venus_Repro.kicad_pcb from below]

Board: 2 copper layers, 175.8 x 60.5 mm, 101 parts (41 on the bottom side), 210 nets.

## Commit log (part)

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2026-02-03 Create LICENCE
    Added CERN OHL S V2 license
2026-02-03 Typo corrections.
2026-03-25 Updated Schematic thanks to insight from Oleg Endo
2026-03-25 Added Gerbers in a zip file

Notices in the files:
Venus_Repro.kicad_pcb:
Licence: CERN-OHL-S
